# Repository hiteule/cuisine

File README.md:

# Cuisine

Ce repo contient les ressources créés pour modifier la cuisine en bois de mon fils : https://twitter.com/hiteule/status/970345943072690176

* cuisine.sch : Schematic Eagle de la carte électronique
* cuisine.brd : Board Eagle de la carte électronique
* cuisine.ino : Code à faire tourner sur un Arduino Nano ou tout autre carte à microcontrôleur AVR

La carte a été pensée pour être alimenté en 12v afin de contrôler deux bandes de LEDs fonctionnant à la même tension.
Attention, l'emplacement des mosfet n'est pas prévu pour accueillir des radiateurs, on ne peux donc pas tirer un courant trop important.

Deux boutons poussoirs à LED doivent être connectés pour servir de commande. Il n'y a pas de résistance de tirage car celles-ci sont intégrées à l'Arduino Nano.

L'afficheur de type 7 segments est drivé par un TM1637.

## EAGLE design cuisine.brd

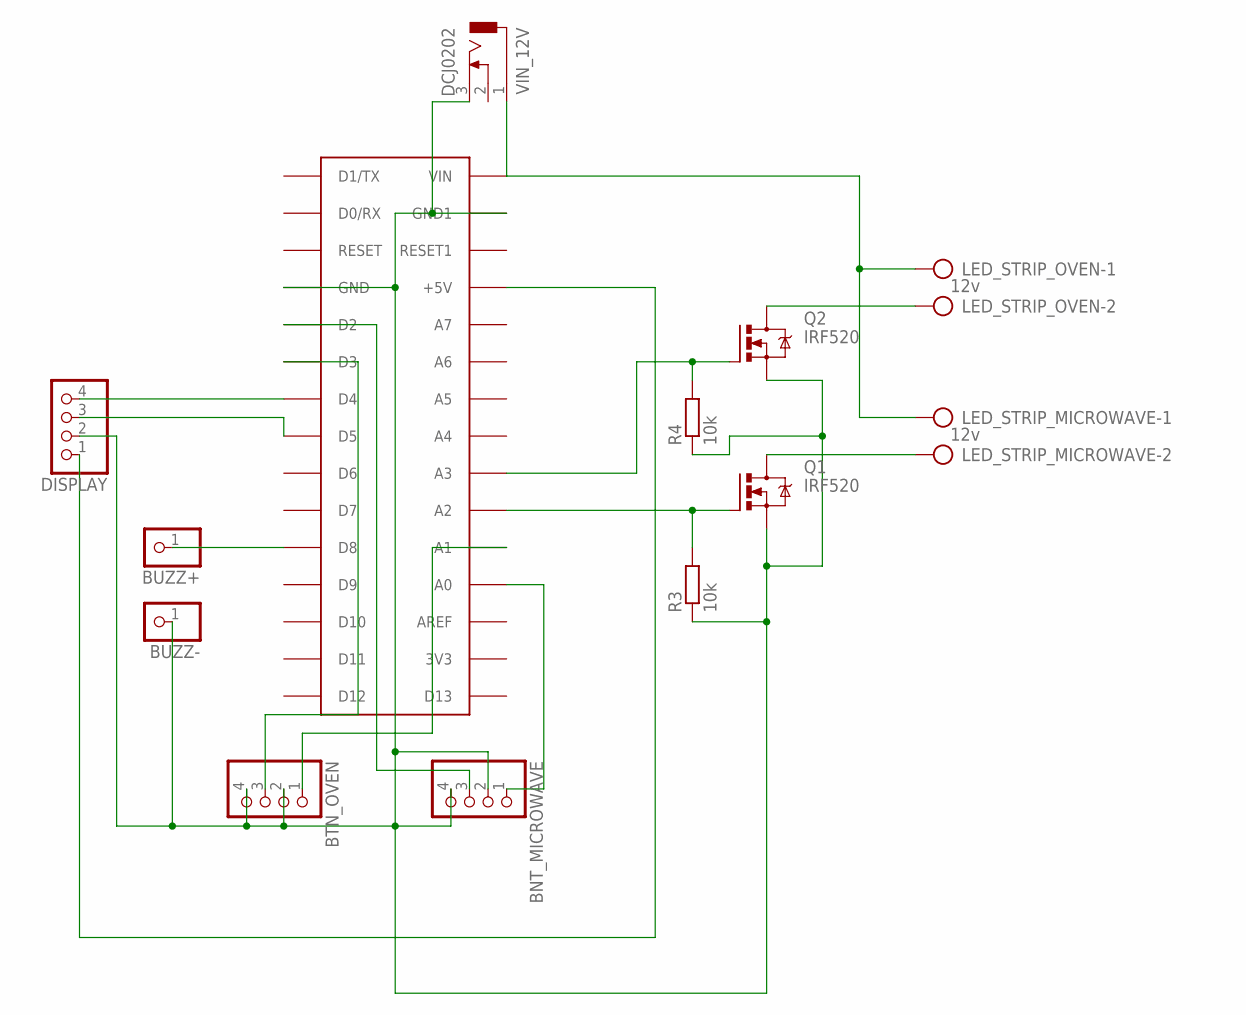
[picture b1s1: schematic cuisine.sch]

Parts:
BNT_MICROWAVE: PINHD-1X4; 1X04
BTN_OVEN: PINHD-1X4; 1X04
BUZZ+: PINHD-1X1; 1X01
BUZZ-: PINHD-1X1; 1X01
DISPLAY: PINHD-1X4; 1X04
LED_STRIP_MICROWAVE: 12v; AK500/2
LED_STRIP_OVEN: 12v; AK500/2
NANO: ARDUINONANO; PDIP-32
Q1, Q2: IRF520; TO220BV
R3, R4: 10k; 0204/7
VIN_12V: DCJ0202

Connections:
unnamed: BNT_MICROWAVE.1, NANO.A0
unnamed: BNT_MICROWAVE.3, NANO.D2
unnamed: BTN_OVEN.1, NANO.A1
unnamed: BNT_MICROWAVE.2, BNT_MICROWAVE.4, BTN_OVEN.2, BTN_OVEN.4, BUZZ-.1, DISPLAY.2, NANO.GND, NANO.GND1, Q1.S, Q2.S, R3.1, R4.1, VIN_12V.3
unnamed: BTN_OVEN.3, NANO.D3
unnamed: NANO.A2, Q1.G, R3.2
unnamed: DISPLAY.1, NANO.+5V
unnamed: DISPLAY.4, NANO.D4
unnamed: DISPLAY.3, NANO.D5
unnamed: LED_STRIP_MICROWAVE.2, Q1.D
unnamed: NANO.A3, Q2.G, R4.2
unnamed: LED_STRIP_MICROWAVE.1, LED_STRIP_OVEN.1, NANO.VIN, VIN_12V.1
unnamed: LED_STRIP_OVEN.2, Q2.D
unnamed: BUZZ+.1, NANO.D8

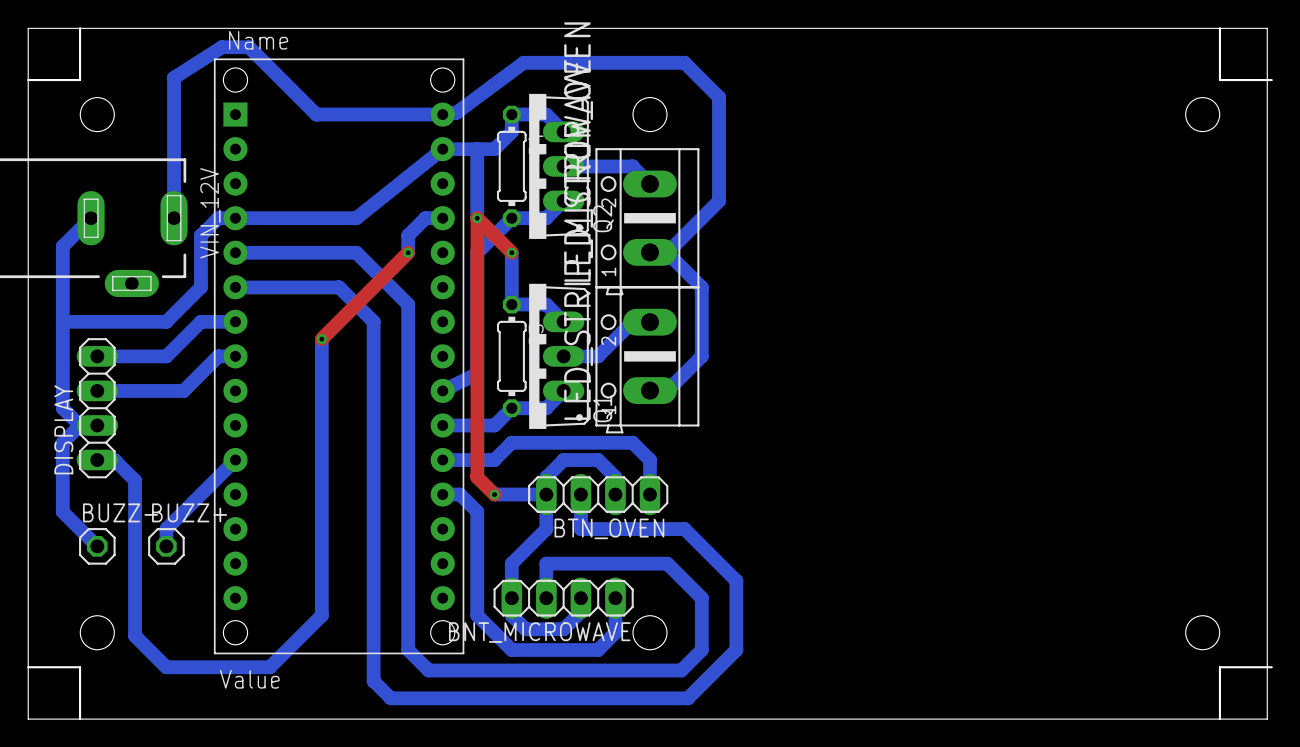
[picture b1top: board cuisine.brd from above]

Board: 2 copper layers, 91.4 x 50.8 mm, 13 parts (0 on the bottom side), 14 nets.

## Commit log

2018-03-19 Rafraichissement de l'afficheur du micro-ondes après incrémentation du compteur et augmentation de la tempo entre les interruptions pour une meilleur KX (Kid eXperience)
